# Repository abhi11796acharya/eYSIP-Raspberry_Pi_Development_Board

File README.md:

***
# eYSIP-2016
# Raspberry pi Hardware Development & Tutorials

### Code
#####  [Accessing GPIO pins of an RPi](https://github.com/eYSIP-2016/eYSIP-Raspberry_Pi_Development_Board/tree/master/Code/Accessing%20GPIO%20pins%20of%20an%20RPi)
*  [Interfacing LED](https://github.com/eYSIP-2016/eYSIP-Raspberry_Pi_Development_Board/tree/master/Code/2.%20Accessing%20GPIO%20pins%20of%20an%20RPi/Interfacing%20LED)
*  [Interfacing led and push button](https://github.com/eYSIP-2016/eYSIP-Raspberry_Pi_Development_Board/tree/master/Code/2.%20Accessing%20GPIO%20pins%20of%20an%20RPi/Interfacing%20Push%20button)
*  [Interfacing Push button](https://github.com/eYSIP-2016/eYSIP-Raspberry_Pi_Development_Board/tree/master/Code/2.%20Accessing%20GPIO%20pins%20of%20an%20RPi/Interfacing%20led%20and%20push%20button)

#####  [IO_port_expander_experiments](https://github.com/eYSIP-2016/eYSIP-Raspberry_Pi_Development_Board/tree/master/Code/IO_port_expander_experiments)
*  [Lcd_With_Mcp23017](https://github.com/eYSIP-2016/eYSIP-Raspberry_Pi_Development_Board/tree/master/Code/IO_port_expander_experiments/Lcd_With_Mcp23017)
*  [Switch_Led_With_Mcp23017](https://github.com/eYSIP-2016/eYSIP-Raspberry_Pi_Development_Board/tree/master/Code/IO_port_expander_experiments/Switch_Led_With_Mcp23017)

#####  ADC Interfacing
* [Interface IR sensor](https://github.com/eYSIP-2016/eYSIP-Raspberry_Pi_Development_Board/tree/master/Code/ADC%20Interfacing/Interface%20IR%20sensor)
* [Interface temperature sensor](https://github.com/eYSIP-2016/eYSIP-Raspberry_Pi_Development_Board/tree/master/Code/ADC%20Interfacing/Interface%20temperature%20sensor)
* [Interface two ADC IC](https://github.com/eYSIP-2016/eYSIP-Raspberry_Pi_Development_Board/tree/master/Code/ADC%20Interfacing/Interface%20two%20ADC%20IC)

#####  Xbee_and_Bluetooth Communication
* Bluetooth and Xbee Communication

#####  Interfacing_DC_MOTOR_with_RPi
* Interface DC motor through MCP23017

#####  Motor control using PWM
* PWM to DC motor through GPIO pins
* PWM to DC motor through PCA9685 IC
* PWM to servo motor through PCA9685 IC

#####  Interrupt
* GPIO pin Interrupt
* Interrupt on RPi through Arduino
* Interrupt using threading

### Documentation
##### Poster
##### Progress Presentation-I
##### Project Report

### PCB Design
##### ADC Interfacing
##### LCD and led interfacing using MCP23017
##### PWM_PCA9685
##### Xbee and bluetooth
##### Ghostviewer Files
##### PCB using SMD components

### Tutorials
##### Document
* RPi_OS_Installation
* Accessing GPIO pins of an RPi
* I2C_Enabling
* IO_port_expander_experiments
* SPI_Enabling_and_basics
* ADC Interfacing
* Xbee_and_Bluetooth Communication
* Interfacing_DC_MOTOR_with_RPi
* Motor control using PWM
* Interrupt
##### Video Tutorial

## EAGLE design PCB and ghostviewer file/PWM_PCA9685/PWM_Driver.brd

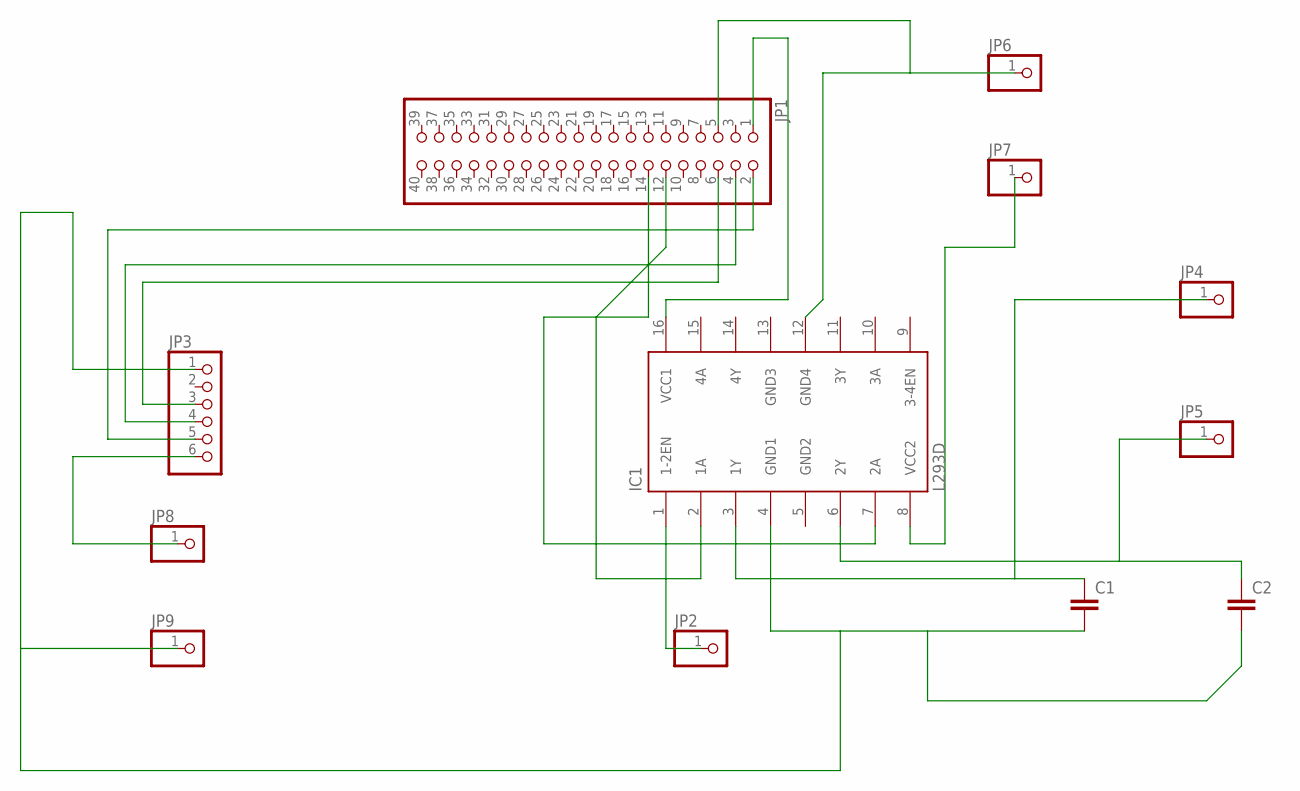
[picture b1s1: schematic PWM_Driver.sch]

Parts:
C1, C2: C5/5; C5B5
IC1: L293D; DIL16
JP1: PINHD-2X20; 2X20
JP2, JP4, JP5, JP6, JP7, JP8, JP9: PINHD-1X1; 1X01
JP3: PINHD-1X6; 1X06

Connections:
GND2: IC1.5 (GND2)
GND3: IC1.13 (GND3)
unnamed: IC1.12 (GND4), JP1.5, JP6.1
unnamed: JP1.2, JP3.5
unnamed: JP1.4, JP3.4
unnamed: JP1.6, JP3.3
unnamed: IC1.1 (1-2EN), JP2.1
unnamed: C1.1, IC1.3 (1Y), JP4.1
unnamed: C2.1, IC1.6 (2Y), JP5.1
unnamed: C1.2, C2.2, IC1.4 (GND1), JP3.1, JP9.1
unnamed: JP3.6, JP8.1
unnamed: IC1.8 (VCC2), JP7.1
unnamed: IC1.16 (VCC1), JP1.1
unnamed: IC1.2 (1A), JP1.12
unnamed: IC1.7 (2A), JP1.14

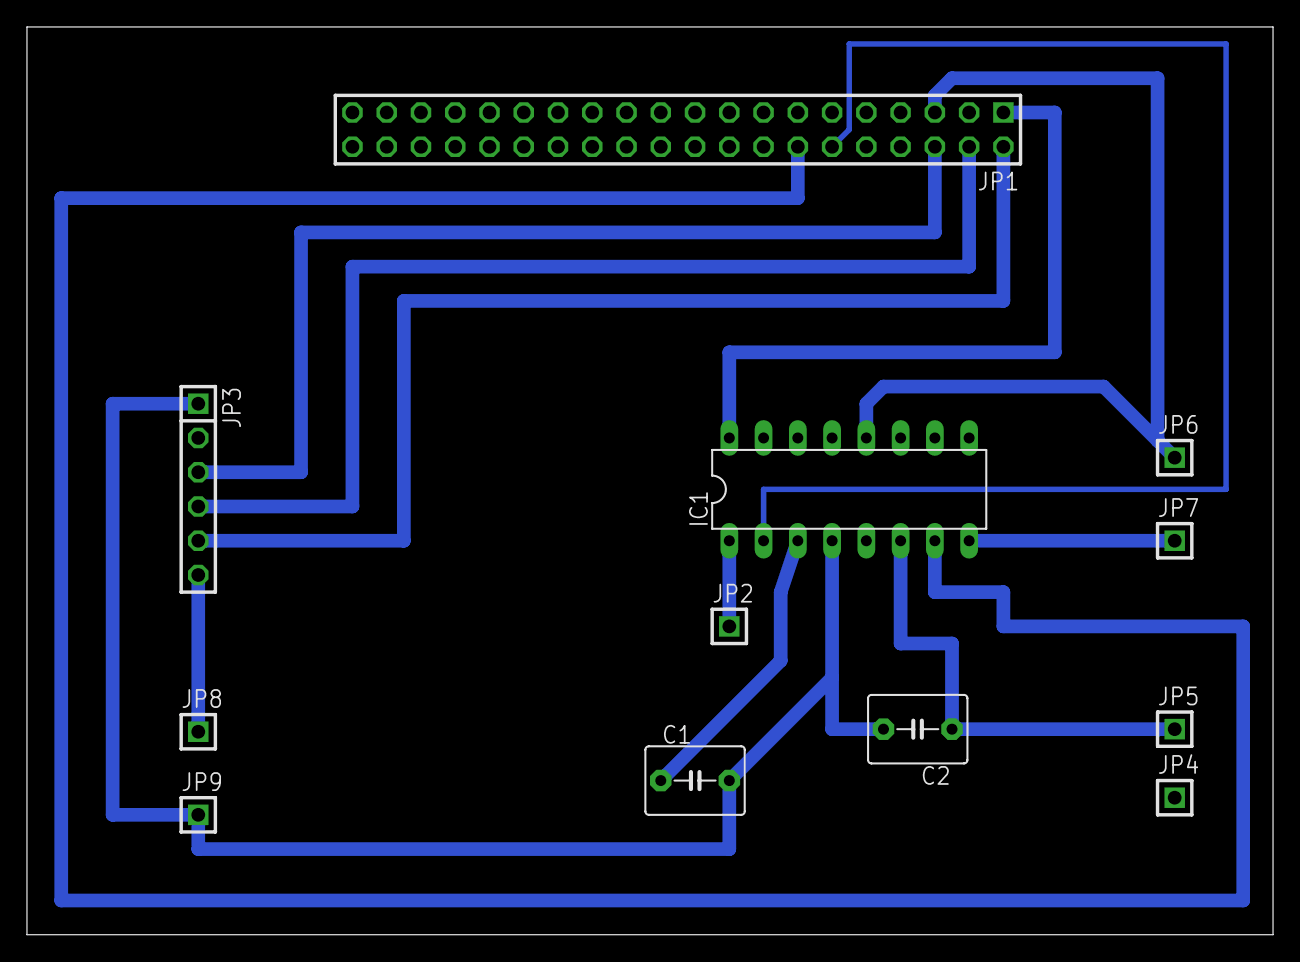
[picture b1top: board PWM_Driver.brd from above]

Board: 2 copper layers, 92.4 x 67.3 mm, 12 parts (0 on the bottom side), 13 nets.

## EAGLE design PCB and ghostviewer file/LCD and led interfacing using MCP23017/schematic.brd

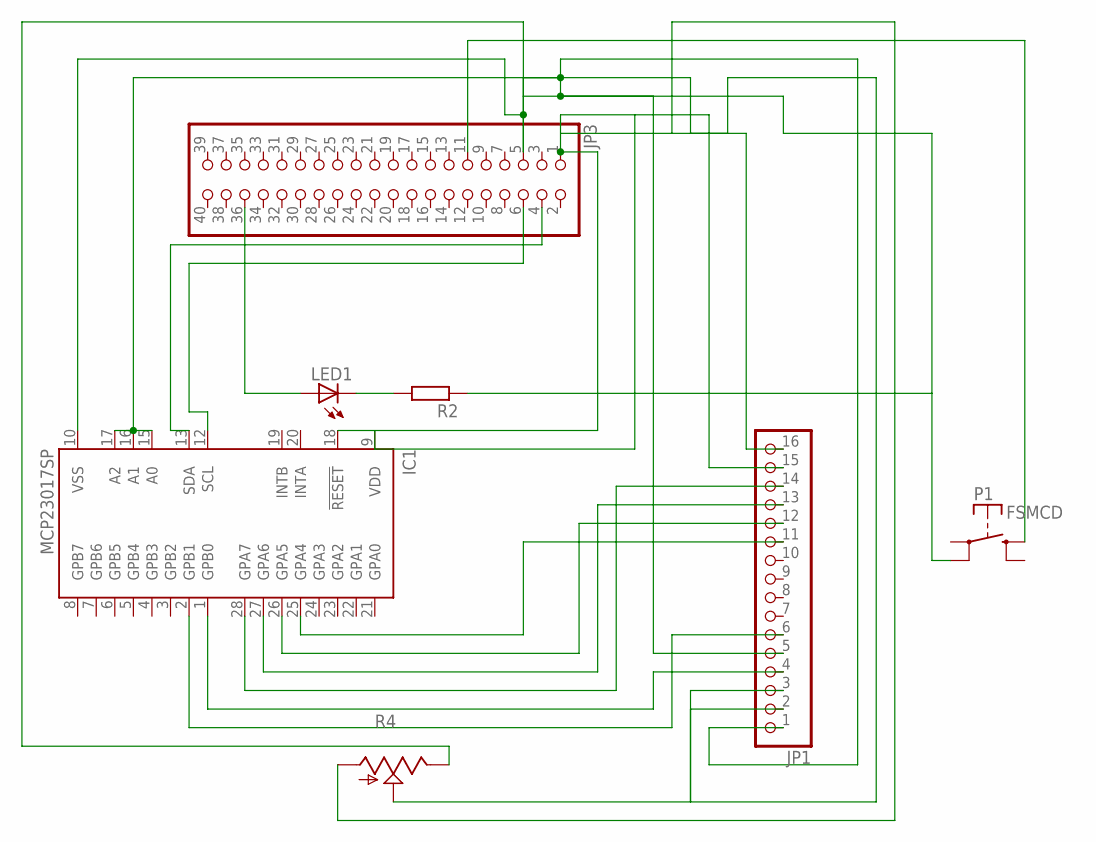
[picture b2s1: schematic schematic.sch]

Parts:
IC1: MCP23017SP; DIL28-3
JP1: PINHD-1X16; 1X16
JP3: PINHD-2X20; 2X20
LED1: LED5MM
P1: FSMCD
R2: R-EU_0207/10; 0207/10
R4: TRIM_US-RS3; RS3

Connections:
unnamed: IC1.25 (GPA4), JP1.11
unnamed: IC1.26 (GPA5), JP1.12
unnamed: IC1.27 (GPA6), JP1.13
unnamed: IC1.28 (GPA7), JP1.14
unnamed: JP1.3, R4.S
unnamed: IC1.1 (GPB0), JP1.4
unnamed: IC1.2 (GPB1), JP1.6
unnamed: IC1.9 (VDD), IC1.18 (!RESET), JP1.15, JP3.1
unnamed: LED1.K (C), R2.2
unnamed: IC1.12 (SCL), JP3.6
unnamed: IC1.13 (SDA), JP3.4
unnamed: JP3.36, LED1.A
unnamed: JP3.11, P1.P$3 (S)
unnamed: JP1.2, R4.A
unnamed: IC1.10 (VSS), IC1.15 (A0), IC1.16 (A1), IC1.17 (A2), JP1.1, JP1.5, JP1.16, JP3.5, P1.P$2, R2.1, R4.E

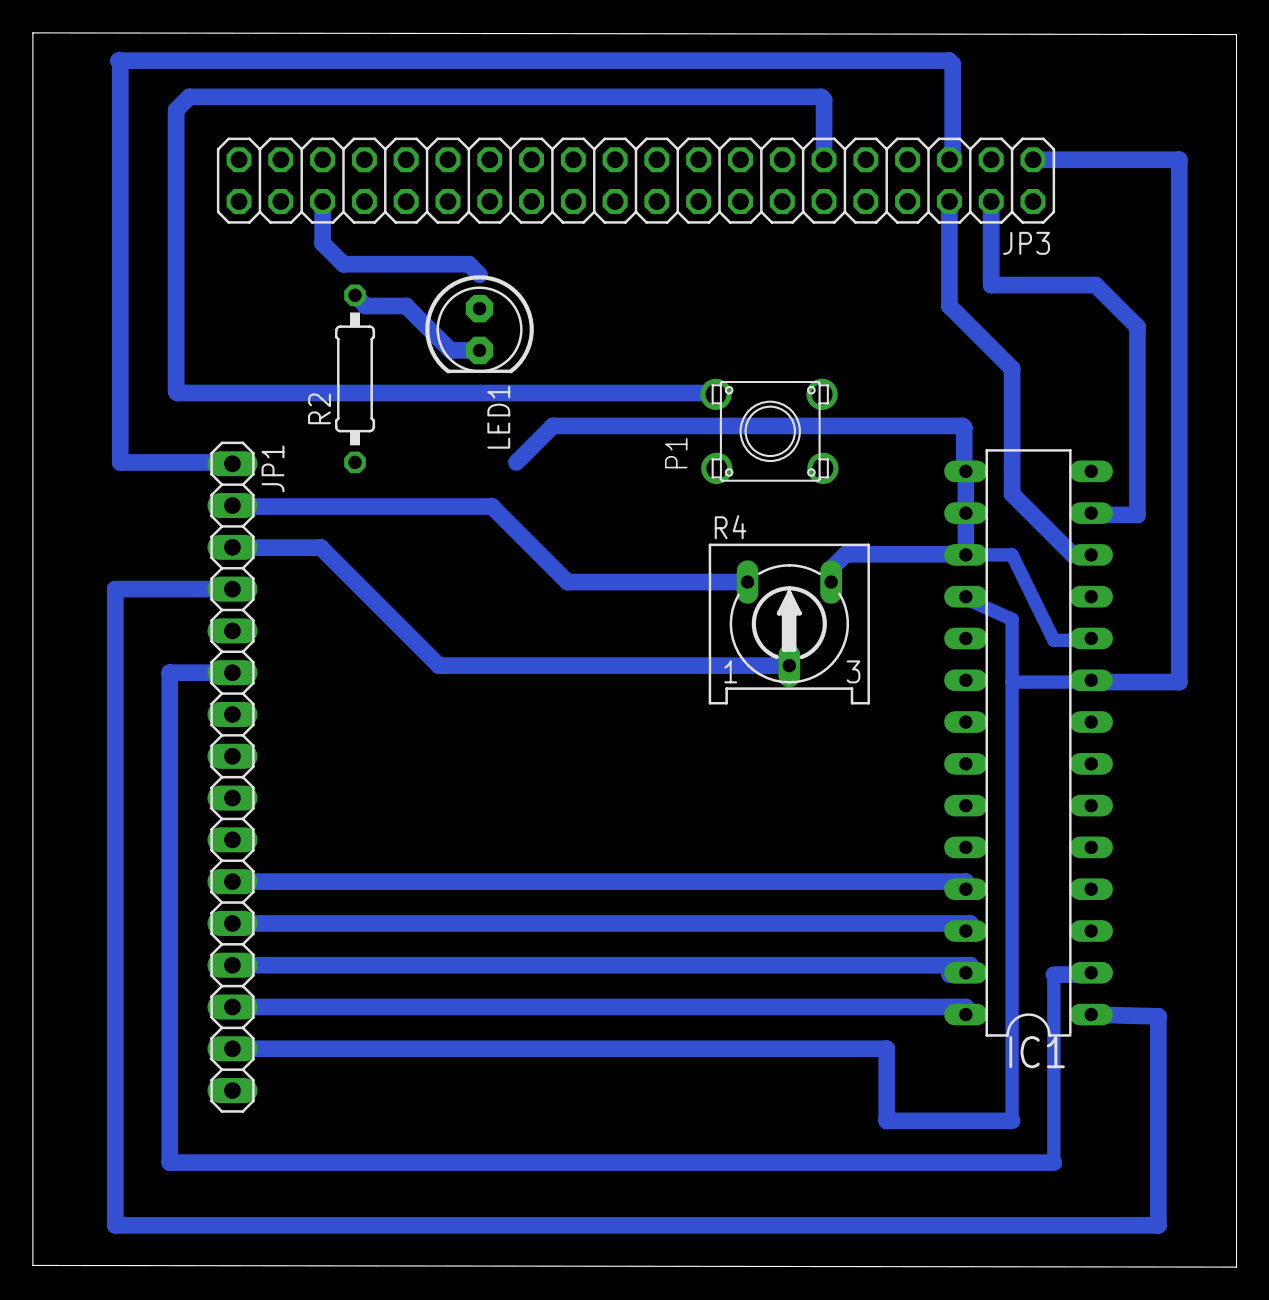
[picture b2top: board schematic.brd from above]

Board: 2 copper layers, 73.2 x 75.0 mm, 7 parts (0 on the bottom side), 15 nets.

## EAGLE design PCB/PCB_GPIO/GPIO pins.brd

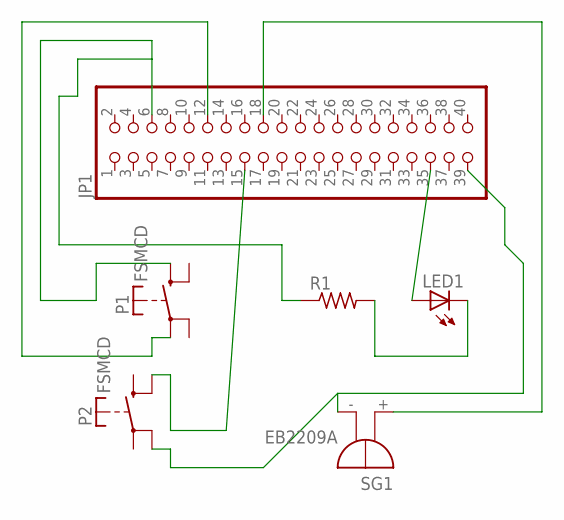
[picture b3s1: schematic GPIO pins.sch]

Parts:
JP1: PINHD-2X20; 2X20
LED1: LED5MM
P1, P2: FSMCD
R1: R-US_0207/5V; 0207/5V
SG1: EB2209A

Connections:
unnamed: JP1.35, LED1.A
unnamed: LED1.K (C), R1.2
unnamed: JP1.18, SG1.+
unnamed: JP1.12, P1.P$1
unnamed: JP1.15, P2.P$4 (S)
unnamed: JP1.39, P2.P$2, SG1.-
unnamed: JP1.6, P1.P$3 (S), R1.1

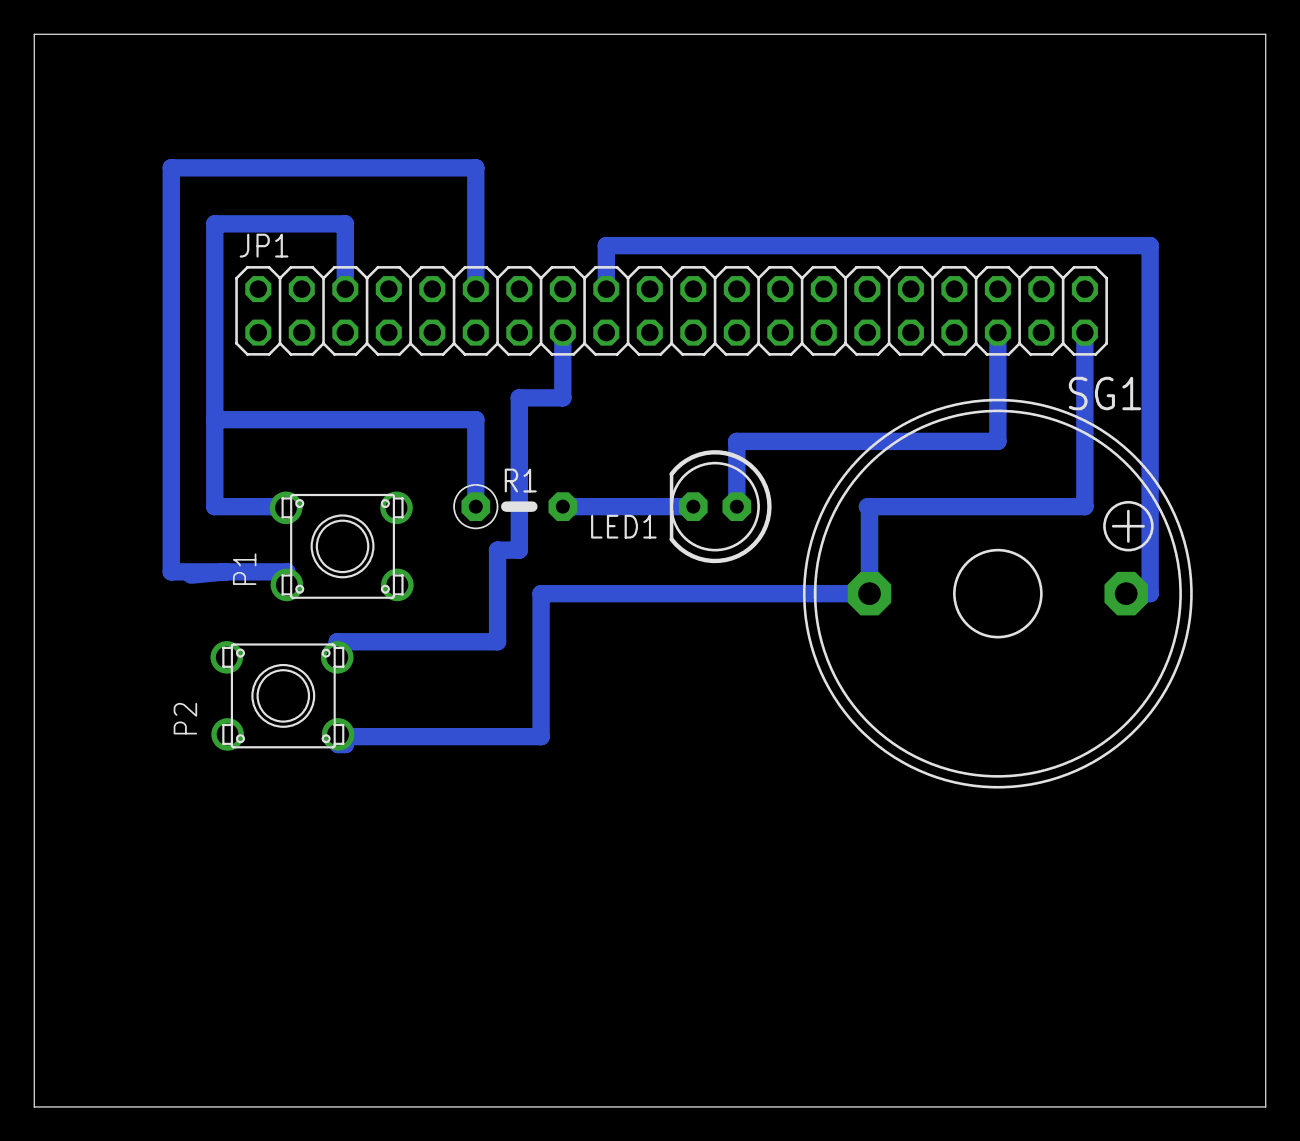
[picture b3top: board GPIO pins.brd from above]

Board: 2 copper layers, 71.9 x 62.6 mm, 6 parts (0 on the bottom side), 7 nets.

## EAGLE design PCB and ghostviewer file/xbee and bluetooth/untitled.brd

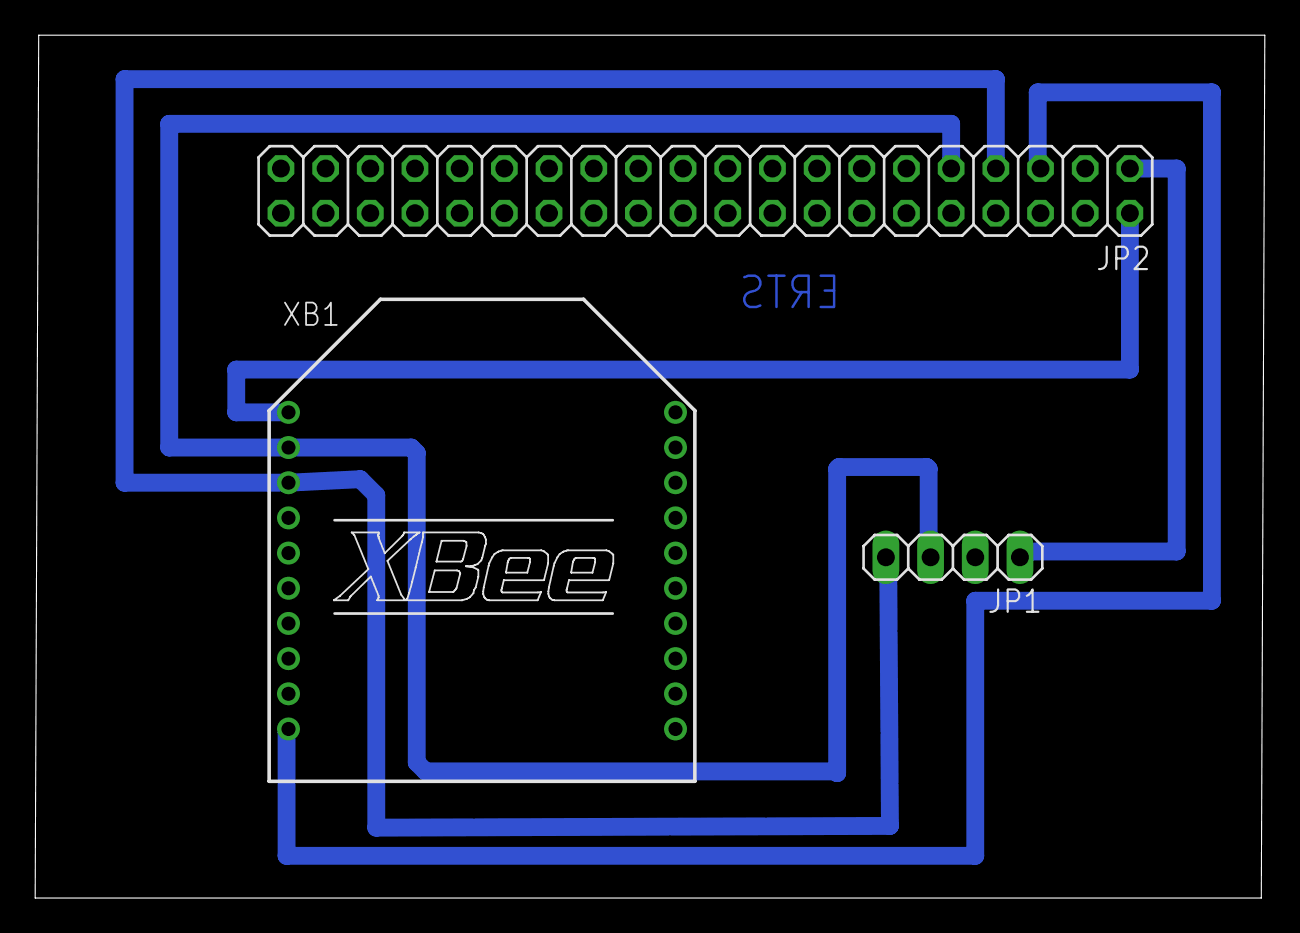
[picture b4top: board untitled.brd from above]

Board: 2 copper layers, 69.9 x 49.0 mm, 3 parts (0 on the bottom side), 5 nets.

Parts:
JP1: 1X04
JP2: 2X20
XB1: XBEE

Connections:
unnamed: JP2.2, XB1.1
unnamed: JP1.2, JP2.5, XB1.10
unnamed: JP1.3, JP2.9, XB1.2
unnamed: JP1.1, JP2.1
unnamed: JP1.4, JP2.7, XB1.3

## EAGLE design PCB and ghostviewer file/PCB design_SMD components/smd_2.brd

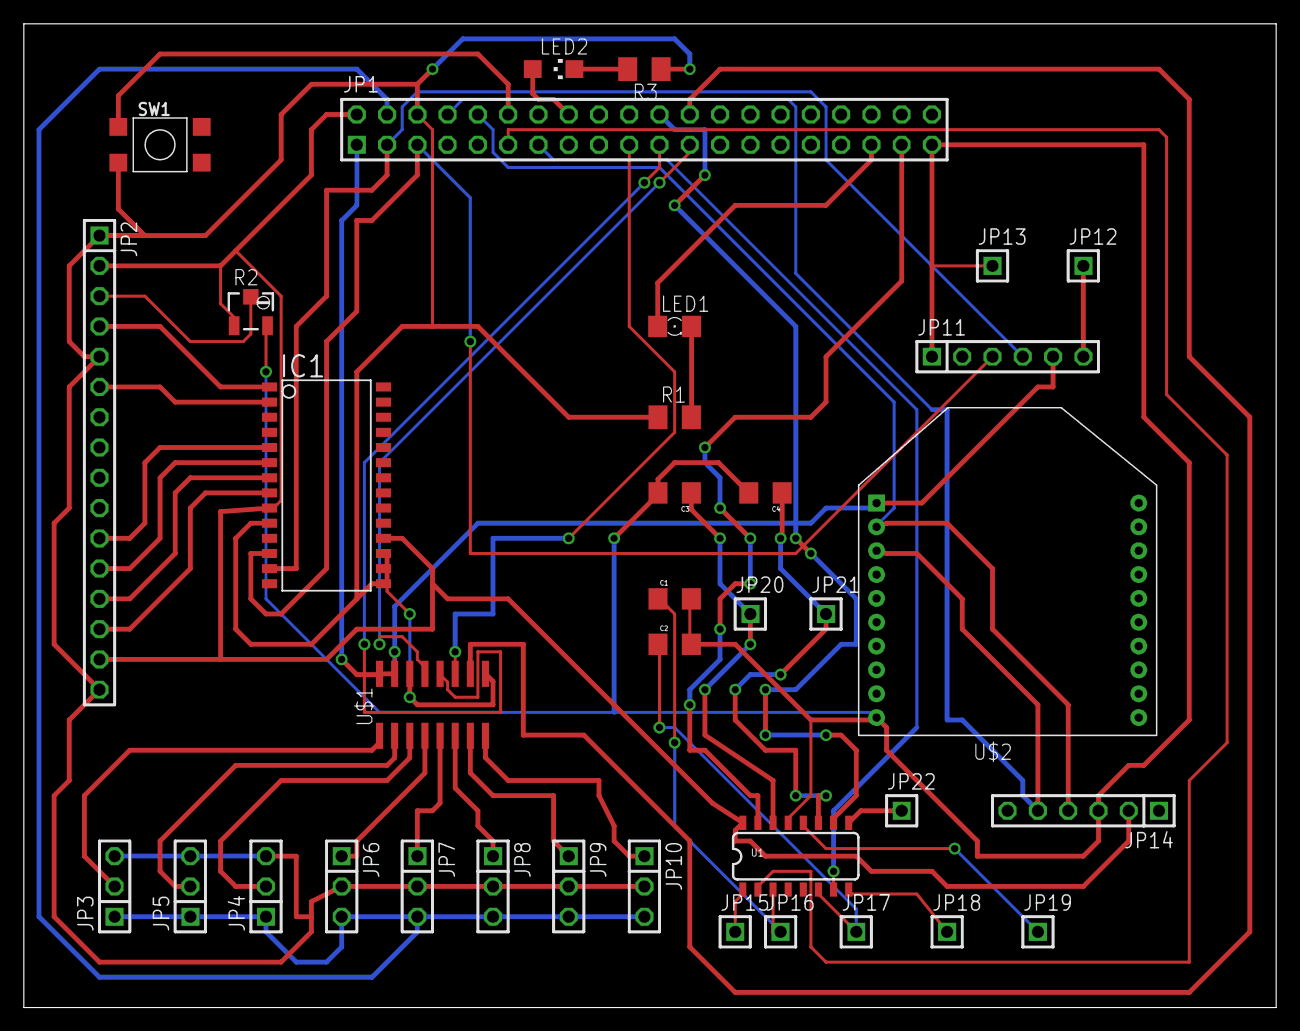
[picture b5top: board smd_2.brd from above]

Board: 2 copper layers, 105.1 x 82.5 mm, 36 parts (0 on the bottom side), 46 nets.

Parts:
C1, C2, C3, C4: 1206
IC1: MCP23017SO; SO28W
JP1: 2X20
JP2: 1X16
JP3, JP4, JP5, JP6, JP7, JP8, JP9, JP10: 1X03
JP11, JP14: 1X06
JP12, JP13, JP15, JP16, JP17, JP18, JP19, JP20, JP21, JP22: 1X01
LED1: 1206
LED2: CHIPLED_1206
R1, R3: M1206
R2: 3223W
SW1: BT4.5X4.5
U1: SN74HC251_SMD; SO016
U$1: MCP3008SL; SO16
U$2: XBEE

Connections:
GND: C1.2, C2.2, C3.2, C4.2, JP1.39, JP11.1, JP13.1, JP14.3, R2.3, U1.13, U$2.10
unnamed: IC1.10, IC1.15, IC1.16, IC1.17, JP1.6, JP2.1, JP2.5, JP2.16, JP3.3, JP4.3, JP5.3, JP6.2, JP7.2, JP8.2, JP9.2, JP10.2, R1.1, R3.1, SW1.S, U$1.9, U$1.14
unnamed: IC1.9, IC1.18, JP1.2, JP2.2, JP2.15, JP14.2, R2.1, U1.16
unnamed: JP1.12, SW1.P
unnamed: IC1.12, JP1.5, JP11.3
unnamed: IC1.13, JP1.3, JP11.4
unnamed: IC1.1, JP2.4
unnamed: IC1.2, JP2.6
unnamed: LED1.C, R1.2
unnamed: JP1.35, LED1.A
unnamed: IC1.8, JP2.14
unnamed: IC1.7, JP2.13
unnamed: IC1.6, JP2.12
unnamed: IC1.5, JP2.11
unnamed: JP1.10, JP14.4, U$2.2
unnamed: JP1.24, U$1.10
unnamed: JP1.19, U$1.11
unnamed: JP1.21, U$1.12
unnamed: JP1.23, U$1.13
unnamed: JP3.2, U$1.1
unnamed: JP5.2, U$1.2
unnamed: JP4.2, U$1.3
unnamed: JP6.1, U$1.4
unnamed: JP7.1, U$1.5
unnamed: JP8.1, U$1.6
unnamed: JP9.1, U$1.7
unnamed: JP10.1, U$1.8
unnamed: JP1.4, JP3.1, JP4.1, JP5.1, JP6.3, JP7.3, JP8.3, JP9.3, JP10.3
unnamed: JP15.1, U1.1
unnamed: JP11.6, JP12.1
unnamed: JP1.8, JP14.5, U$2.3
unnamed: JP1.11, U1.2
unnamed: JP1.13, U1.7
unnamed: JP18.1, U1.8
unnamed: C1.1, JP16.1, U1.3
unnamed: C2.1, JP17.1, U1.6
unnamed: JP19.1, U1.12
unnamed: JP2.3, R2.2
unnamed: JP1.16, LED2.A
unnamed: LED2.C, R3.2
unnamed: C3.1, JP20.1, U1.14
unnamed: C4.1, JP21.1, U1.11
unnamed: JP1.37, U1.15
unnamed: JP1.22, U1.10
unnamed: JP22.1, U1.9
VCC: JP1.1, JP11.5, U$1.15, U$1.16, U$2.1

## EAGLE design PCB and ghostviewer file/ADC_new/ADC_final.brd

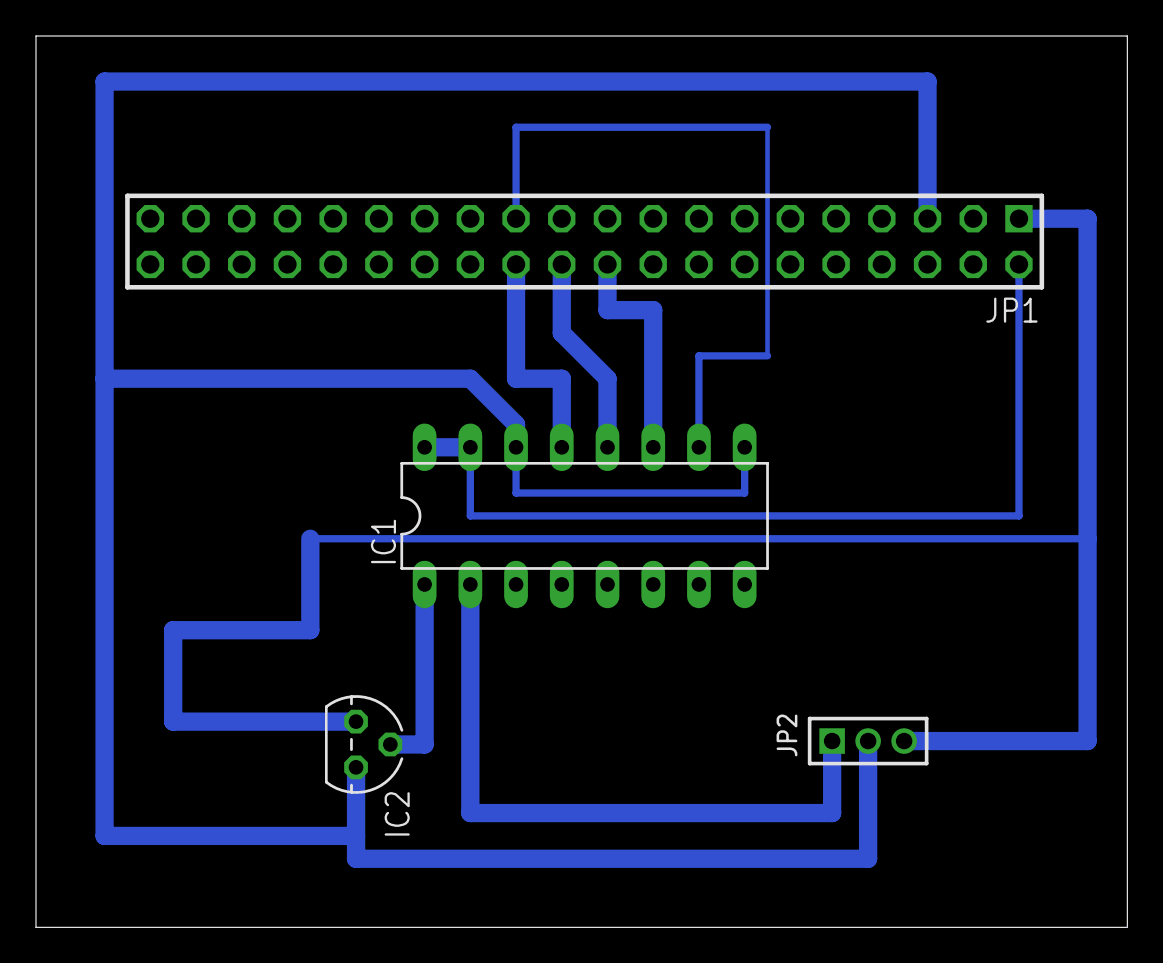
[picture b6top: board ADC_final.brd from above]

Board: 2 copper layers, 60.6 x 49.5 mm, 4 parts (0 on the bottom side), 9 nets.

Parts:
IC1: MCP3008; DIL16
IC2: LM35CZ; TO92
JP1: 2X20
JP2: 1X03M

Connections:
unnamed: IC2.1, JP1.1, JP2.3
unnamed: IC1.15, IC1.16, JP1.2
unnamed: IC1.9, IC1.14, IC2.3, JP1.5, JP2.2
unnamed: IC1.1, IC2.2
unnamed: IC1.2, JP2.1
unnamed: IC1.11, JP1.20
unnamed: IC1.12, JP1.22
unnamed: IC1.13, JP1.24
unnamed: IC1.10, JP1.23

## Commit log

2016-06-01 commit 1
2016-06-02 GPIO pins Document
2016-06-07 ADC, I2C,RPi_OS, SPI
    ADC interfacing, I2C enabling and basics, RPi OS installation and SPI
    enabling
2016-06-08 Interfacing DC Motor
    Interfacing DC motor using L293D motor driver
2016-06-08 PCB_GPIO
    Printed circuit board of GPIO
2016-06-08 PCB_GPIO
2016-06-08 IO_port_expander
    Using MCP23017 IC.
    LCD, LED and switch is interfaced with RPi
2016-06-08 PCB GPIO Final
2016-06-11 Modification
2016-06-11 Xbee Bluetooth Communication
2016-06-24 changes in dc motor document
2016-06-27 video transcript
2016-07-05 Interrupt
2016-07-06 I2c video tutorial
2016-07-07 challege activity
2016-07-07 Changes in PCB
2016-07-07 Added readme
2016-07-08 commented the code of challenge activity
2016-07-08 Datasheet Uploaded
2016-07-08 Final Report
2016-07-09 Project Report
2016-07-09 Rpi Firebird Communication
2016-07-10 Added datasheet and video presentation

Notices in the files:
parts and their libraries:
SparkFun-Capacitors: Licensing: Creative Commons ShareAlike 4.0 International - https://creativecommons.org/licenses/by-sa/4.0
